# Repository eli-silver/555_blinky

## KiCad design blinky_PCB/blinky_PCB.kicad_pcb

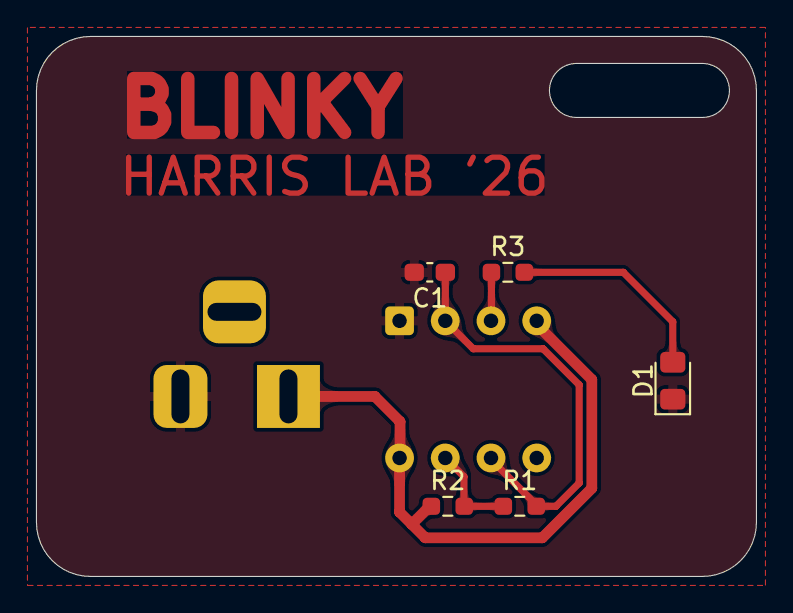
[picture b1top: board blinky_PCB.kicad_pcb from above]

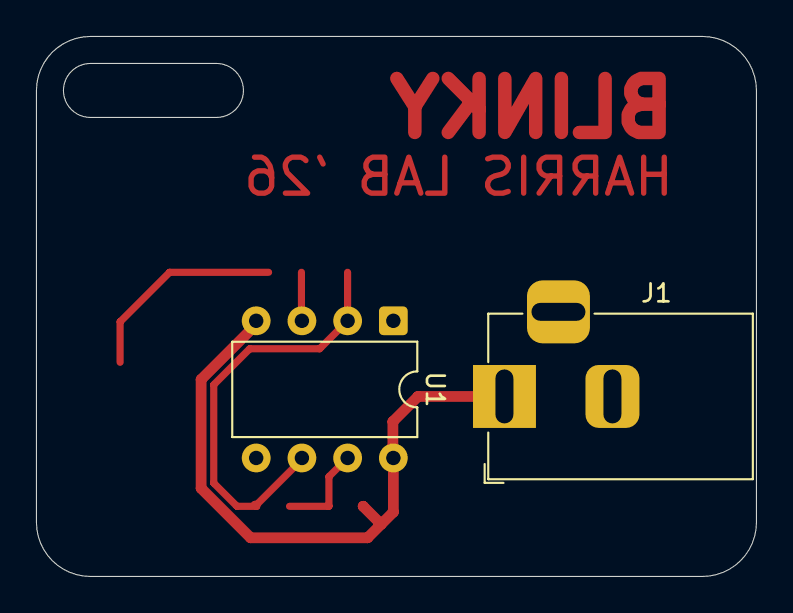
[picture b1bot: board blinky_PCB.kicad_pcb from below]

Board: 2 copper layers, 40.0 x 30.0 mm, 7 parts (2 on the bottom side), 6 nets.

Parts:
C1: 1u; C_0603_1608Metric_Pad1.08x0.95mm_HandSolder
D1: LED; LED_0805_2012Metric_Pad1.15x1.40mm_HandSolder
J1: Barrel_Jack_MountingPin; BarrelJack_Horizontal
R1: 470k; R_0603_1608Metric_Pad0.98x0.95mm_HandSolder
R2: 2k; R_0603_1608Metric_Pad0.98x0.95mm_HandSolder
R3: 330; R_0603_1608Metric_Pad0.98x0.95mm_HandSolder
U1: NE555P; DIP-8_W7.62mm

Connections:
+9V: J1.1, R2.1, U1.4 (~RST), U1.8 (VCC)
GND: C1.2, D1.1 (K), J1.2, U1.1 (GND)
unnamed: D1.2 (A), R3.2
unnamed: R1.1, R2.2, U1.7 (DISCH)
unnamed: R3.1, U1.3 (OUT)
unnamed: C1.1, R1.2, U1.2 (TRIG), U1.6 (THRES)

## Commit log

2026-02-27 pcb milled, progress still to do to optimize file and milling process
2026-02-27 adjusted a few things, design still not finalized
2026-03-05 updated PCB cam
